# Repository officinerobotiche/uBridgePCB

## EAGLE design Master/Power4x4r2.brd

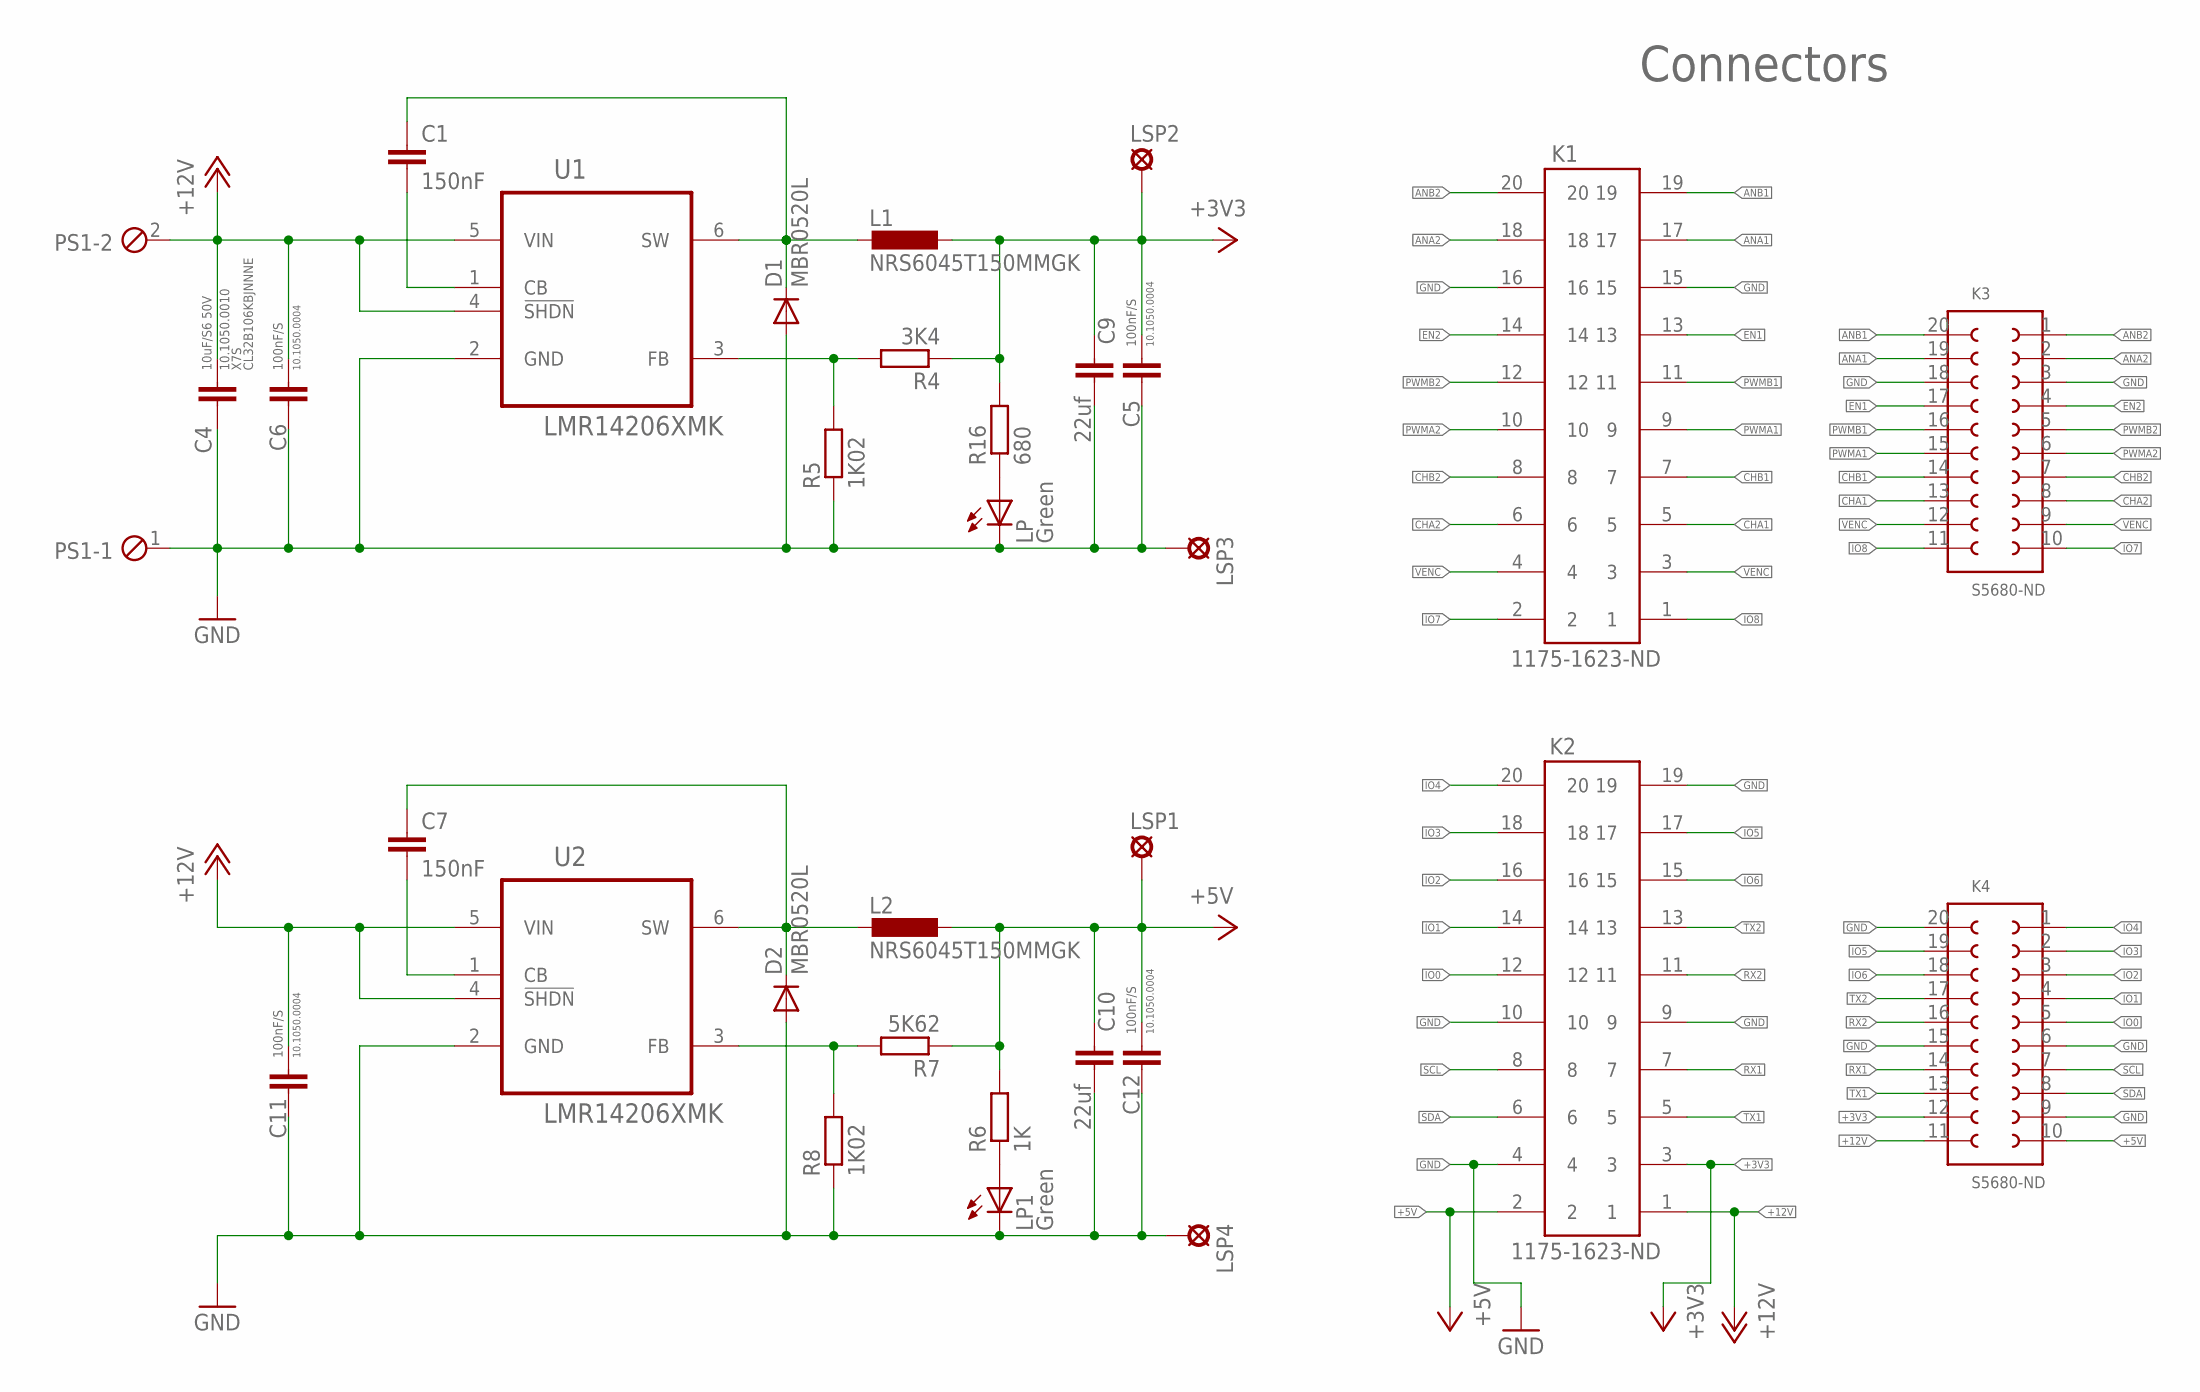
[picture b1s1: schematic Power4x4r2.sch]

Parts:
C1, C7: 150nF; C0805K
C4: 10uF/S6 50V; C3225
C5, C6, C11, C12: 100nF/S; C0805
C9, C10: 22uf; C1206
D1, D2: MBR0520L; SOD123; DIGIKEY MBR0520LCT-ND
K1, K2: 1175-1623-ND; 612X2020621
K3, K4: S5680-ND; 61002021821
L1, L2: NRS6045T150MMGK; POWER-CHOKE_WE-TPC; DIGIKEY 587-2948-1-ND
LP, LP1: Green; CHIPLED_0805
LSP1, LSP2, LSP3, LSP4: LSP10
PS1: MPT2; 2POL254
R4: 3K4; R0805
R5, R8: 1K02; R0805
R6: 1K; R0603
R7: 5K62; R0805
R16: 680; R0603
U1, U2: LMR14206XMK; SOT95P280X110-6N; DIGIKEY LMR14206XMKE/NOPBCT-ND

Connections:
+3V3: C5.2, C9.1, K2.3, K4.12, L1.1, LSP2.MP, R4.1, R16.2
+5V: C10.1, C12.2, K2.2, K4.10, L2.1, LSP1.MP, R6.2, R7.1
+12V: C4.1, C6.2, C11.2, K2.1, K4.11, PS1.2, U1.4 (!SHDN), U1.5 (VIN), U2.4 (!SHDN), U2.5 (VIN)
ANA1: K1.17, K3.19
ANA2: K1.18, K3.2
ANB1: K1.19, K3.20
ANB2: K1.20, K3.1
CHA1: K1.5, K3.13
CHA2: K1.6, K3.8
CHB1: K1.7, K3.14
CHB2: K1.8, K3.7
EN1: K1.13, K3.17
EN2: K1.14, K3.4
GND: C4.2, C5.1, C6.1, C9.2, C10.2, C11.1, C12.1, D1.A, D2.A, K1.15, K1.16, K2.4, K2.9, K2.10, K2.19, K3.3, K3.18, K4.6, K4.9, K4.15, K4.20, LP.C, LP1.C, LSP3.MP, LSP4.MP, PS1.1, R5.1, R8.1, U1.2 (GND), U2.2 (GND)
IO0: K2.12, K4.5
IO1: K2.14, K4.4
IO2: K2.16, K4.3
IO3: K2.18, K4.2
IO4: K2.20, K4.1
IO5: K2.17, K4.19
IO6: K2.15, K4.18
IO7: K1.2, K3.10
IO8: K1.1, K3.11
unnamed: C1.2, U1.1 (CB)
unnamed: C1.1, D1.C, L1.2, U1.6 (SW)
unnamed: LP1.A, R6.1
unnamed: R4.2, R5.2, U1.3 (FB)
unnamed: LP.A, R16.1
unnamed: C7.2, U2.1 (CB)
unnamed: C7.1, D2.C, L2.2, U2.6 (SW)
unnamed: R7.2, R8.2, U2.3 (FB)
PWMA1: K1.9, K3.15
PWMA2: K1.10, K3.6
PWMB1: K1.11, K3.16
PWMB2: K1.12, K3.5
RX1: K2.7, K4.14
RX2: K2.11, K4.16
SCL: K2.8, K4.7
SDA: K2.6, K4.8
TX1: K2.5, K4.13
TX2: K2.13, K4.17
VENC: K1.3, K1.4, K3.9, K3.12

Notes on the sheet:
Connectors

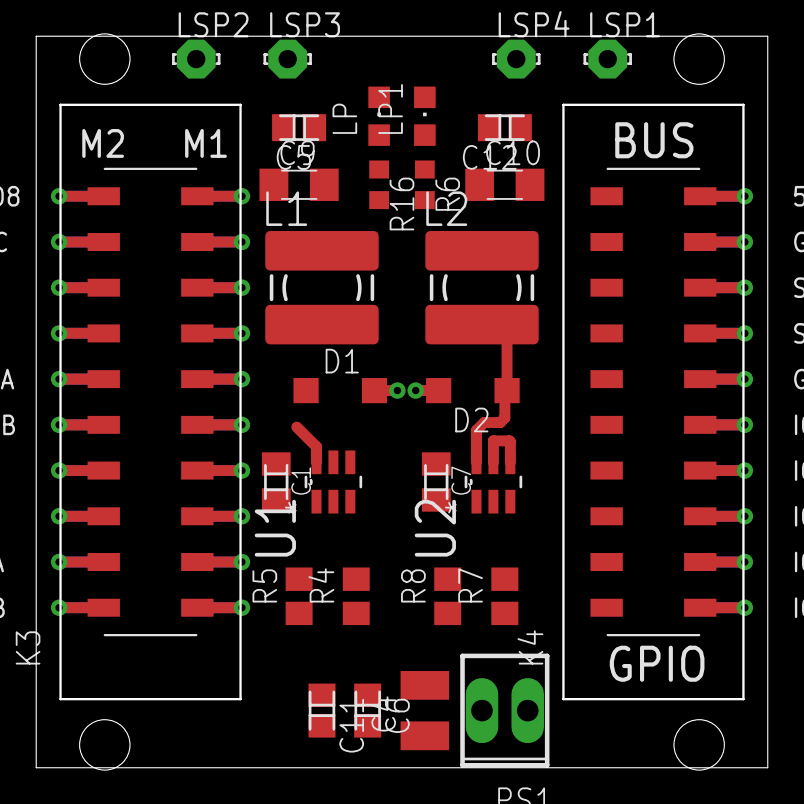
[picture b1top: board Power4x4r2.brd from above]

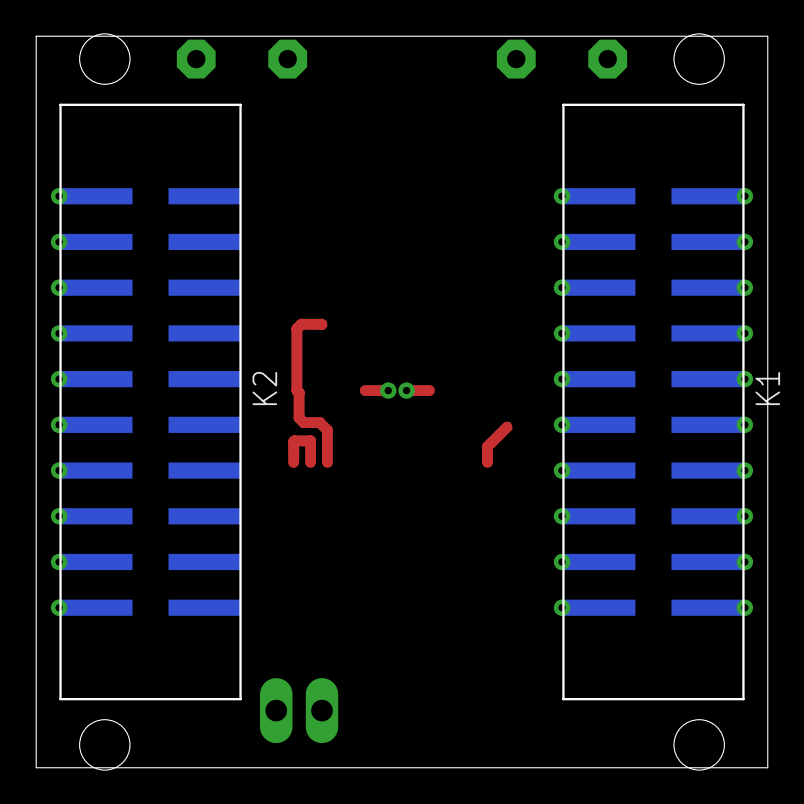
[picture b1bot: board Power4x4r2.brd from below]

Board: 2 copper layers, 40.6 x 40.6 mm, 32 parts (2 on the bottom side), 42 nets.

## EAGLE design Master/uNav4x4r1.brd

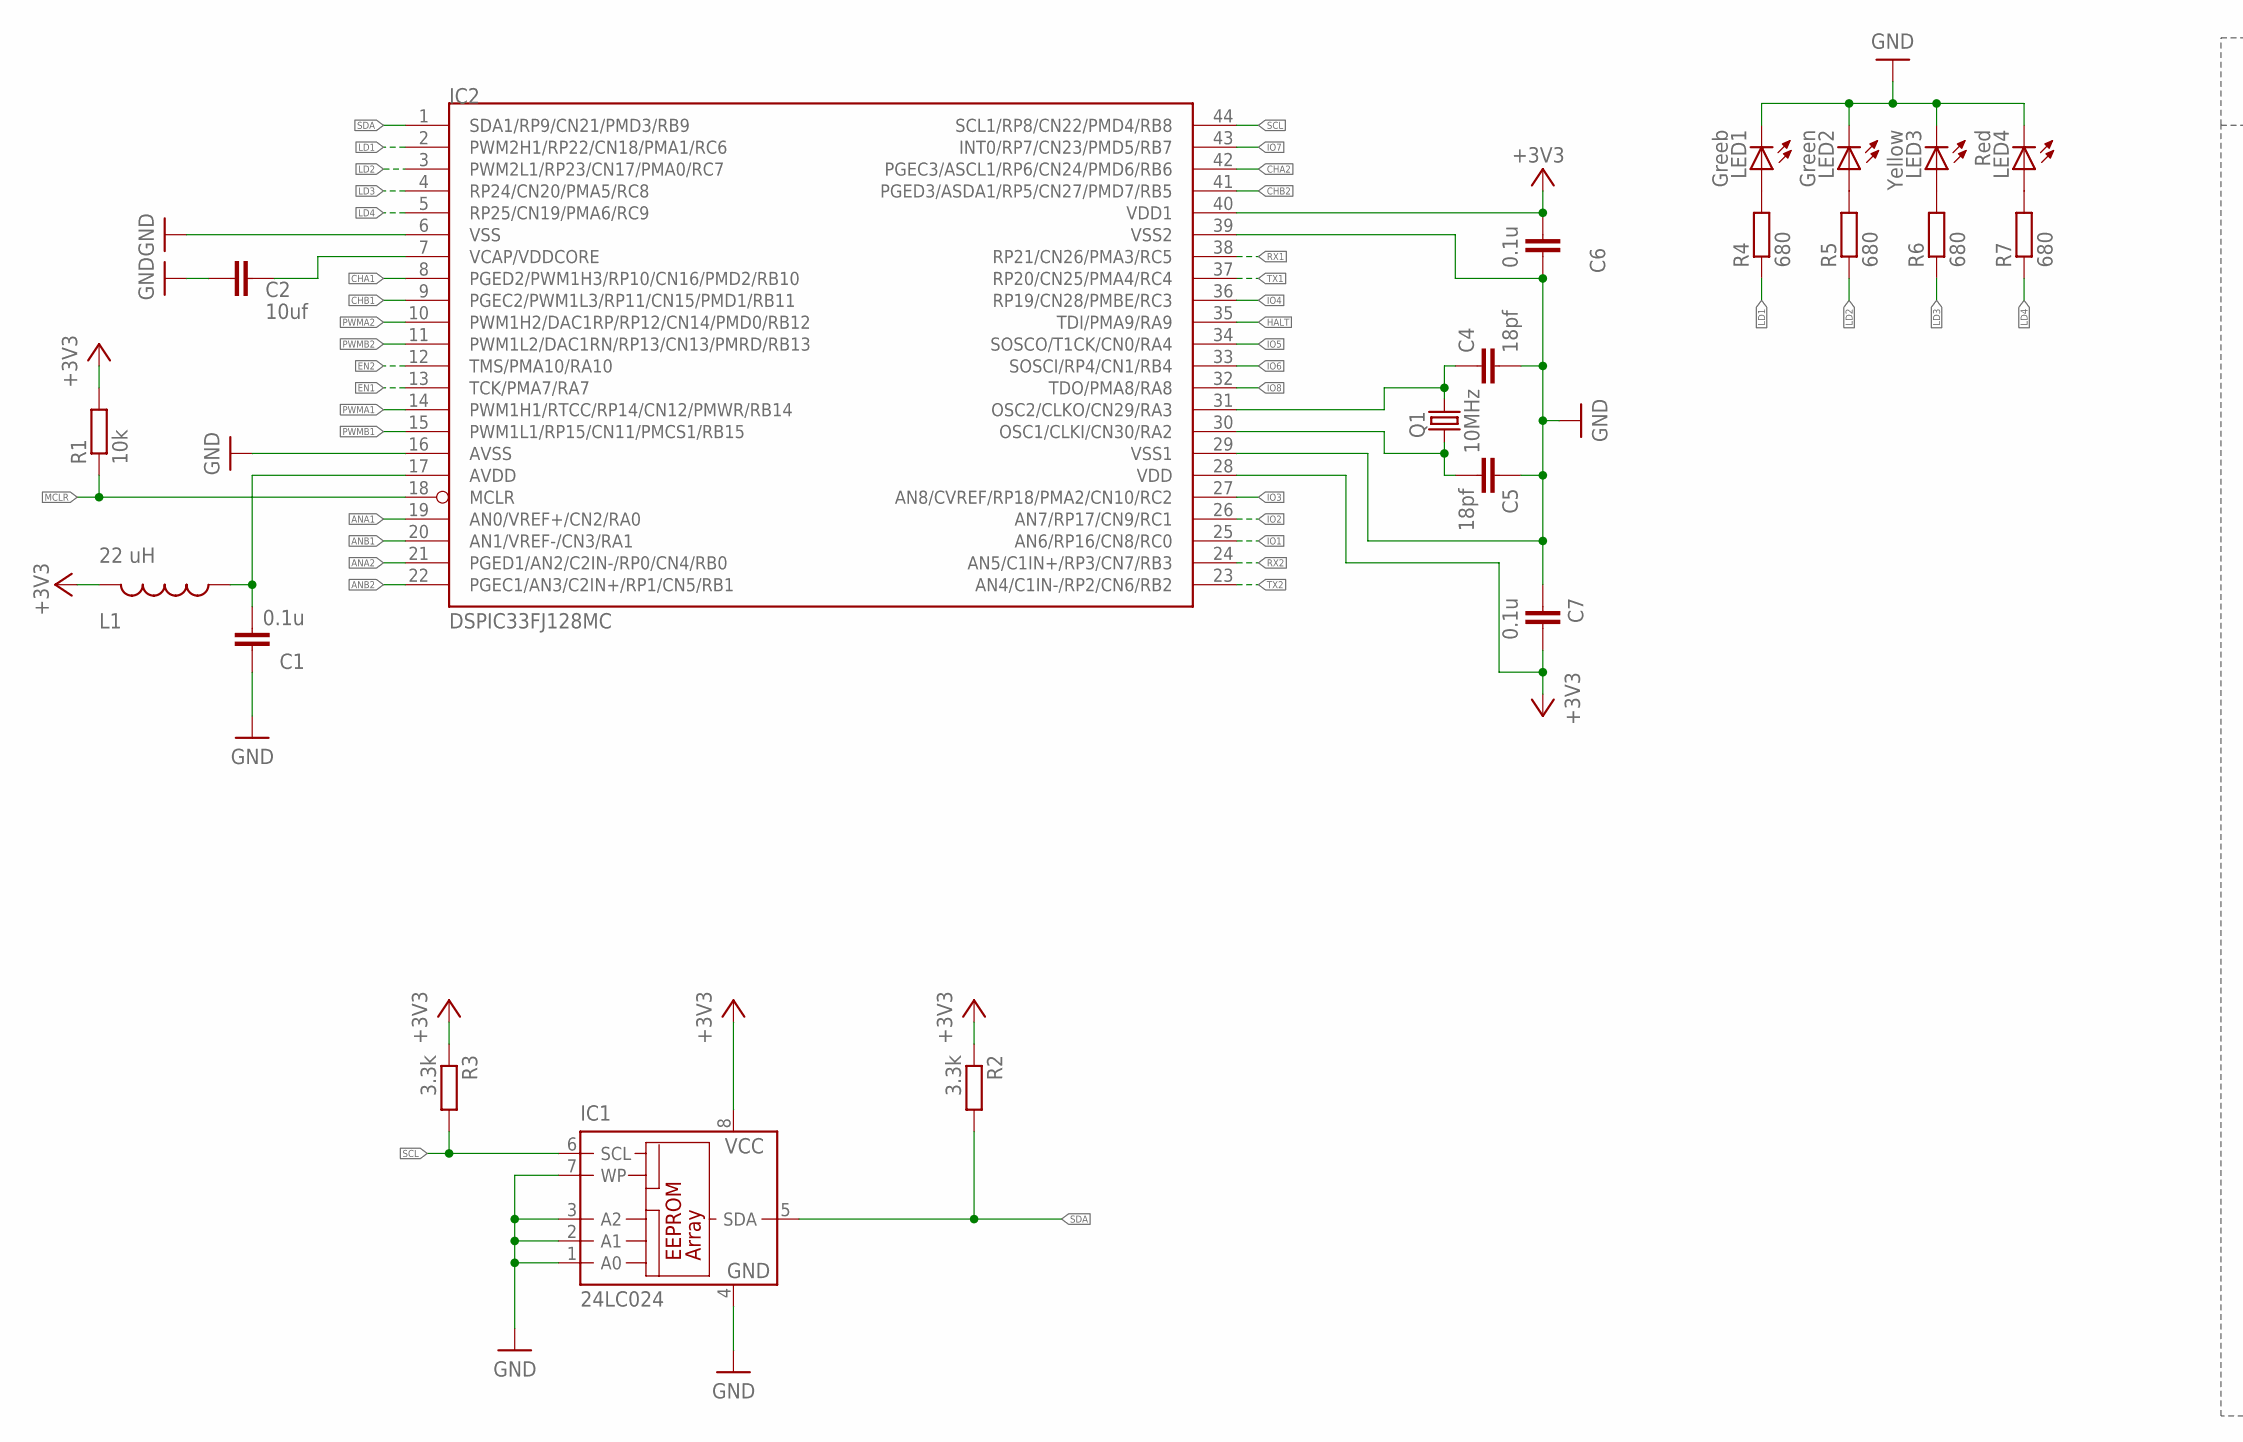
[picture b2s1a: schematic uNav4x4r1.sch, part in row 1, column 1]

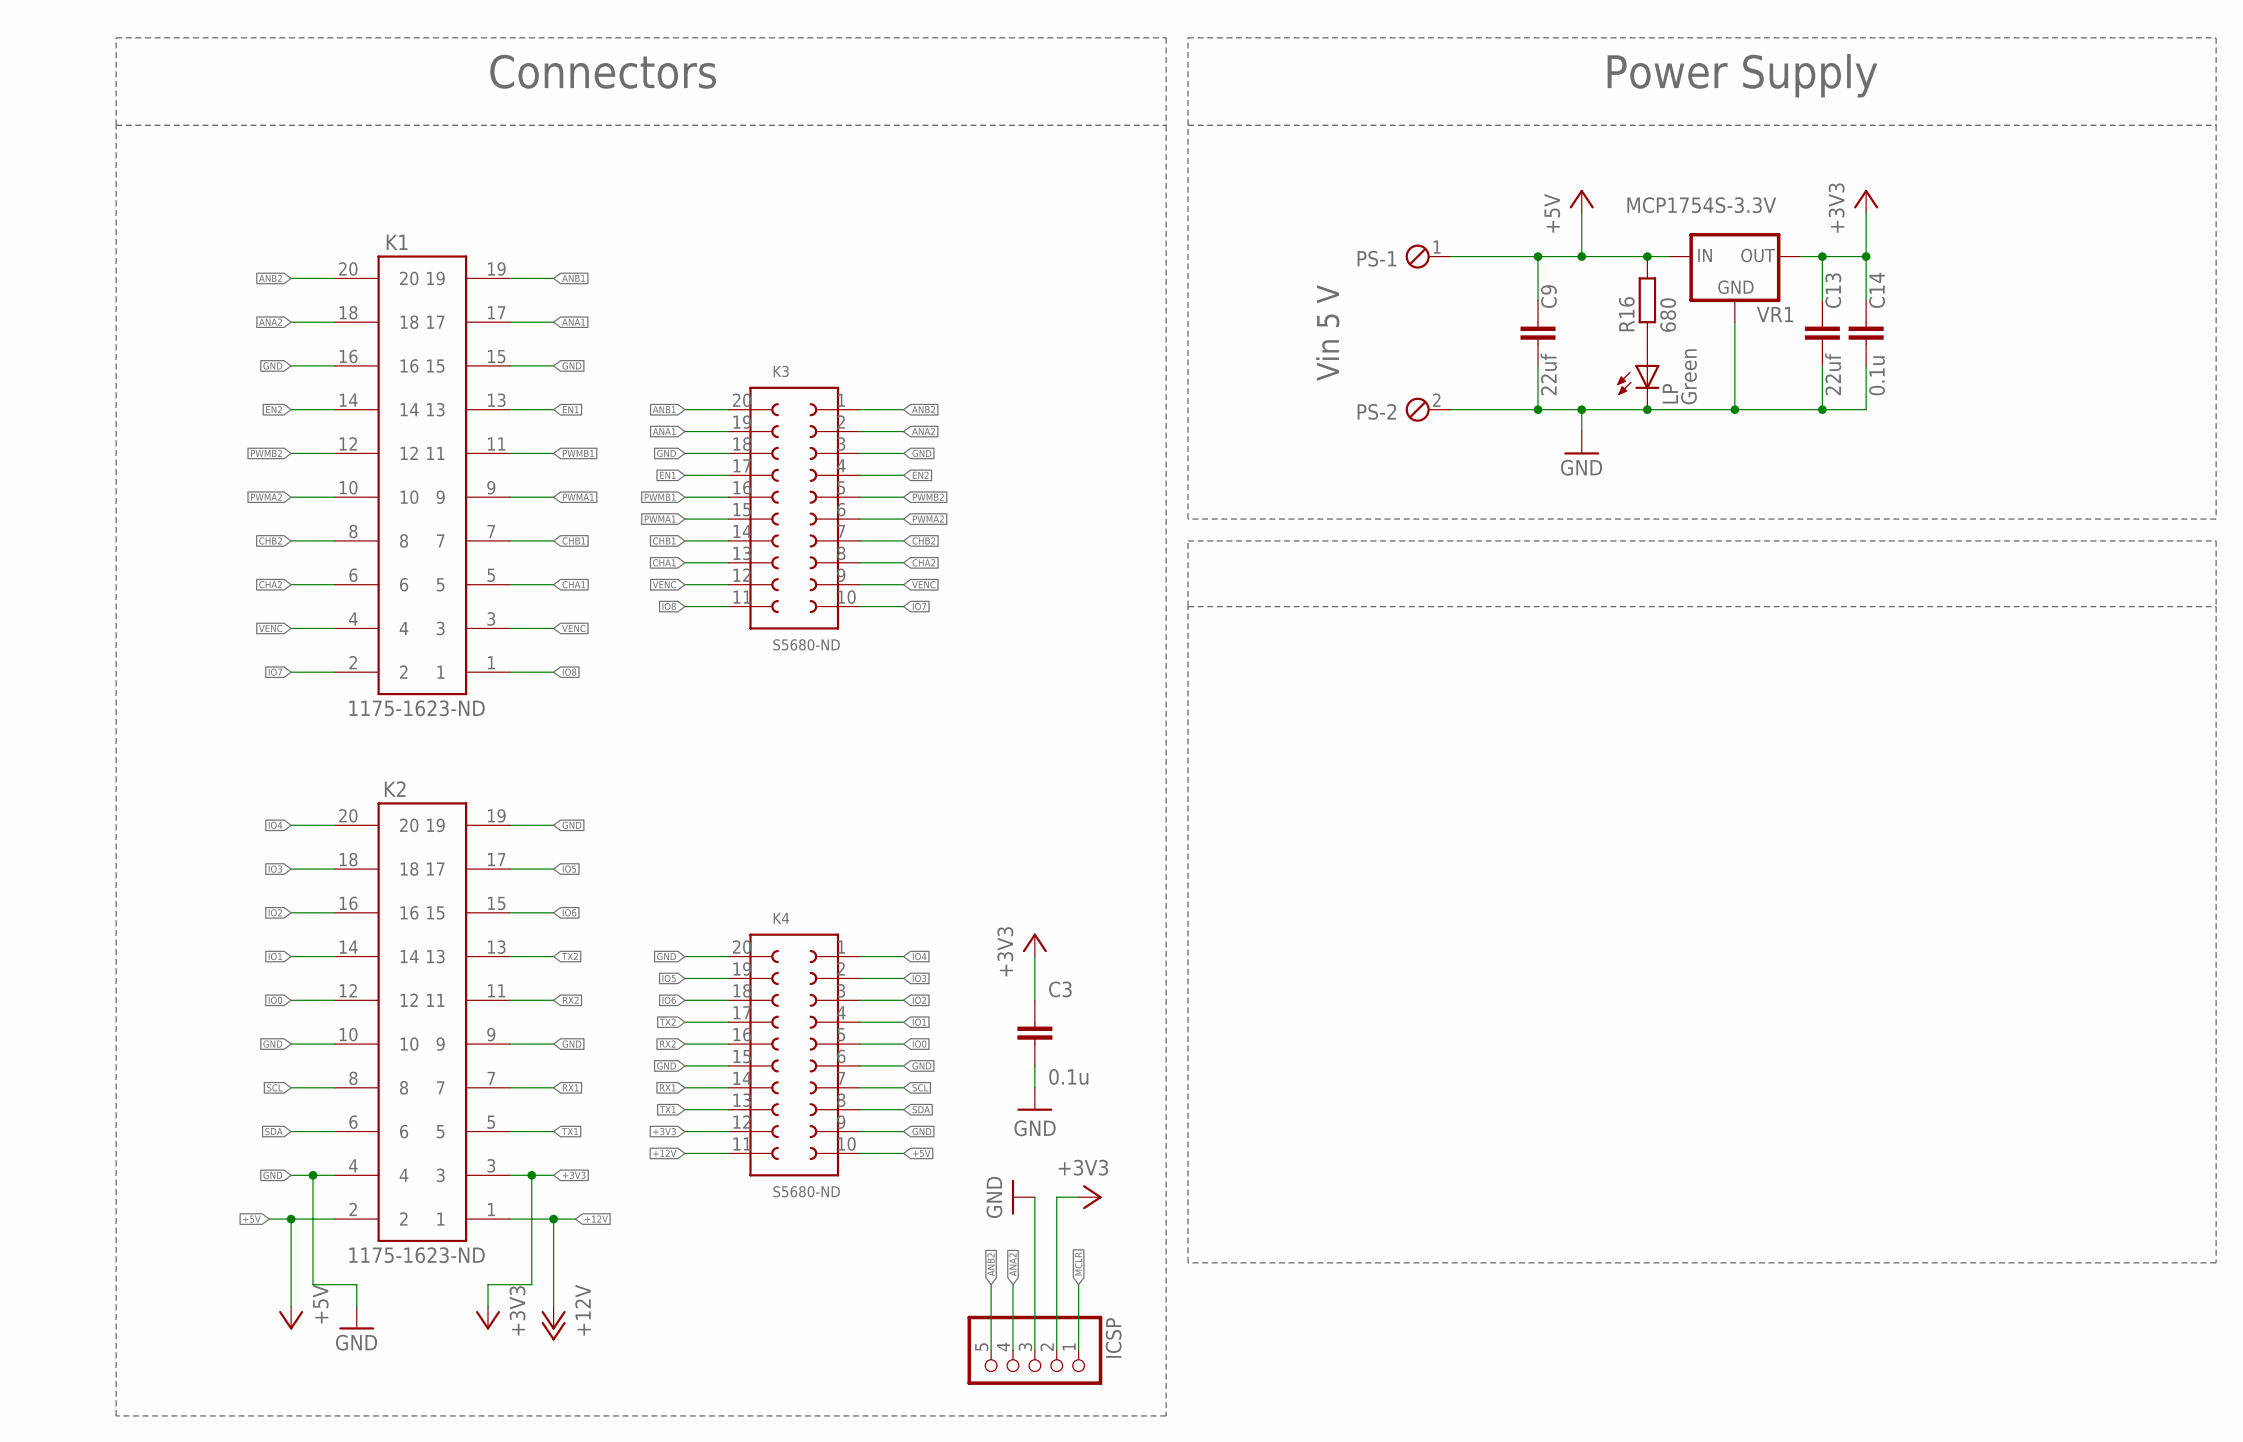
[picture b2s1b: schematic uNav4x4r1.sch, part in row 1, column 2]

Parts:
C1, C3, C6, C7, C14: 0.1u; C0603
C2: 10uf; C1206
C4, C5: 18pf; C0603
C9, C13: 22uf; C1206
IC1: 24LC024; SO-08M
IC2: DSPIC33FJ128MC; TQFP44
ICSP: PINHD-1X05_2.54-S; 1X05-S
K1, K2: 1175-1623-ND; 612X2020621
K3, K4: S5680-ND; 61002021821
L1: 22 uH; 0805
LED1: Greeb; CHIPLED_0805
LED2: Green; CHIPLED_0805
LED3: Yellow; CHIPLED_0805
LED4: Red; CHIPLED_0805
LP: Green; CHIPLED_0805
PS: MPT2; 2POL254
Q1: 10MHz; HC49U-V
R1: 10k; R0603
R2, R3: 3.3k; R0603
R4, R5, R6, R7, R16: 680; R0603
VR1: MCP1754S-3.3V; SOT89

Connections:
+3V3: C3.1, C6.2, C7.1, C13.1, C14.1, IC1.8 (VCC), IC2.28 (VDD), IC2.40 (VDD1), ICSP.2, K2.3, K4.12, L1.2, R1.2, R2.1, R3.1, VR1.3 (OUT)
+5V: C9.1, K2.2, K4.10, PS.1, R16.2, VR1.1 (IN)
+12V: K2.1, K4.11
ANA1: IC2.19 (AN0/VREF+/CN2/RA0), K1.17, K3.19
ANA2: IC2.21 (PGED1/AN2/C2IN-/RP0/CN4/RB0), ICSP.4, K1.18, K3.2
ANB1: IC2.20 (AN1/VREF-/CN3/RA1), K1.19, K3.20
ANB2: IC2.22 (PGEC1/AN3/C2IN+/RP1/CN5/RB1), ICSP.5, K1.20, K3.1
AVDD: C1.2, IC2.17 (AVDD), L1.1
CHA1: IC2.8 (PGED2/PWM1H3/RP10/CN16/PMD2/RB10), K1.5, K3.13
CHA2: IC2.42 (PGEC3/ASCL1/RP6/CN24/PMD6/RB6), K1.6, K3.8
CHB1: IC2.9 (PGEC2/PWM1L3/RP11/CN15/PMD1/RB11), K1.7, K3.14
CHB2: IC2.41 (PGED3/ASDA1/RP5/CN27/PMD7/RB5), K1.8, K3.7
EN1: IC2.13 (TCK/PMA7/RA7), K1.13, K3.17
EN2: IC2.12 (TMS/PMA10/RA10), K1.14, K3.4
GND: C1.1, C2.2, C3.2, C4.2, C5.1, C6.1, C7.2, C9.2, C13.2, C14.2, IC1.1 (A0), IC1.2 (A1), IC1.3 (A2), IC1.4 (GND), IC1.7 (WP), IC2.6 (VSS), IC2.16 (AVSS), IC2.29 (VSS1), IC2.39 (VSS2), ICSP.3, K1.15, K1.16, K2.4, K2.9, K2.10, K2.19, K3.3, K3.18, K4.6, K4.9, K4.15, K4.20, LED1.C, LED2.C, LED3.C, LED4.C, LP.C, PS.2, VR1.2 (GND), VR1.4 (GND)
HALT: IC2.35 (TDI/PMA9/RA9)
IO0: K2.12, K4.5
IO1: IC2.25 (AN6/RP16/CN8/RC0), K2.14, K4.4
IO2: IC2.26 (AN7/RP17/CN9/RC1), K2.16, K4.3
IO3: IC2.27 (AN8/CVREF/RP18/PMA2/CN10/RC2), K2.18, K4.2
IO4: IC2.36 (RP19/CN28/PMBE/RC3), K2.20, K4.1
IO5: IC2.34 (SOSCO/T1CK/CN0/RA4), K2.17, K4.19
IO6: IC2.33 (SOSCI/RP4/CN1/RB4), K2.15, K4.18
IO7: IC2.43 (INT0/RP7/CN23/PMD5/RB7), K1.2, K3.10
IO8: IC2.32 (TDO/PMA8/RA8), K1.1, K3.11
LD1: IC2.2 (PWM2H1/RP22/CN18/PMA1/RC6), R4.1
LD2: IC2.3 (PWM2L1/RP23/CN17/PMA0/RC7), R5.1
LD3: IC2.4 (RP24/CN20/PMA5/RC8), R6.1
LD4: IC2.5 (RP25/CN19/PMA6/RC9), R7.1
MCLR: IC2.18 (MCLR), ICSP.1, R1.1
unnamed: C5.2, IC2.30 (OSC1/CLKI/CN30/RA2), Q1.1
unnamed: C4.1, IC2.31 (OSC2/CLKO/CN29/RA3), Q1.2
unnamed: LP.A, R16.1
unnamed: LED1.A, R4.2
unnamed: LED2.A, R5.2
unnamed: LED3.A, R6.2
unnamed: LED4.A, R7.2
PWMA1: IC2.14 (PWM1H1/RTCC/RP14/CN12/PMWR/RB14), K1.9, K3.15
PWMA2: IC2.10 (PWM1H2/DAC1RP/RP12/CN14/PMD0/RB12), K1.10, K3.6
PWMB1: IC2.15 (PWM1L1/RP15/CN11/PMCS1/RB15), K1.11, K3.16
PWMB2: IC2.11 (PWM1L2/DAC1RN/RP13/CN13/PMRD/RB13), K1.12, K3.5
RX1: IC2.38 (RP21/CN26/PMA3/RC5), K2.7, K4.14
RX2: IC2.24 (AN5/C1IN+/RP3/CN7/RB3), K2.11, K4.16
SCL: IC1.6 (SCL), IC2.44 (SCL1/RP8/CN22/PMD4/RB8), K2.8, K4.7, R3.2
SDA: IC1.5 (SDA), IC2.1 (SDA1/RP9/CN21/PMD3/RB9), K2.6, K4.8, R2.2
TX1: IC2.37 (RP20/CN25/PMA4/RC4), K2.5, K4.13
TX2: IC2.23 (AN4/C1IN-/RP2/CN6/RB2), K2.13, K4.17
VCAP/VDDCORE: C2.1, IC2.7 (VCAP/VDDCORE)
VENC: K1.3, K1.4, K3.9, K3.12

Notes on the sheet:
Connectors
Vin 5 V
Power Supply

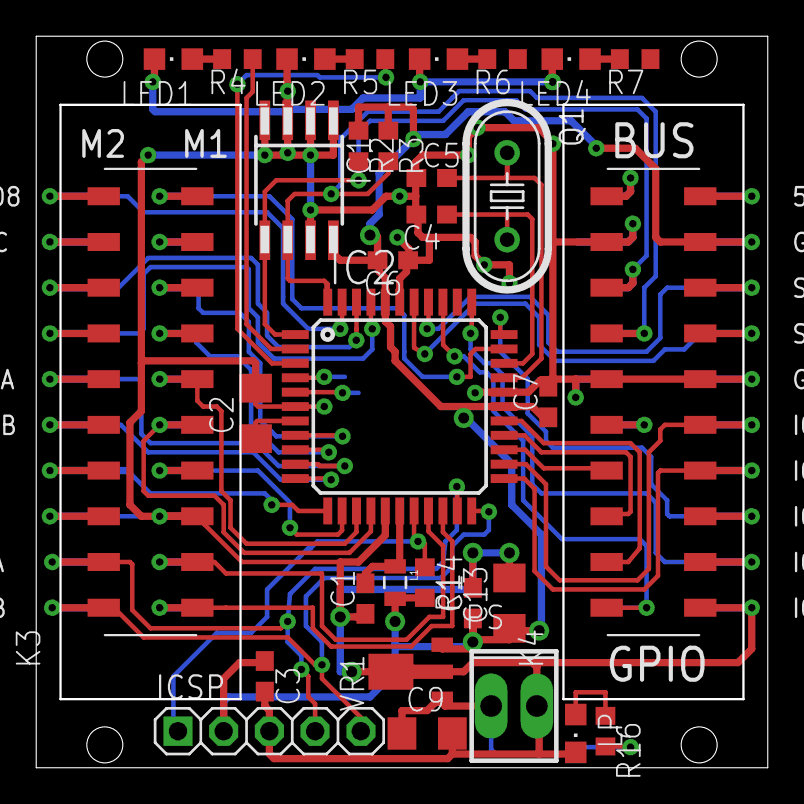
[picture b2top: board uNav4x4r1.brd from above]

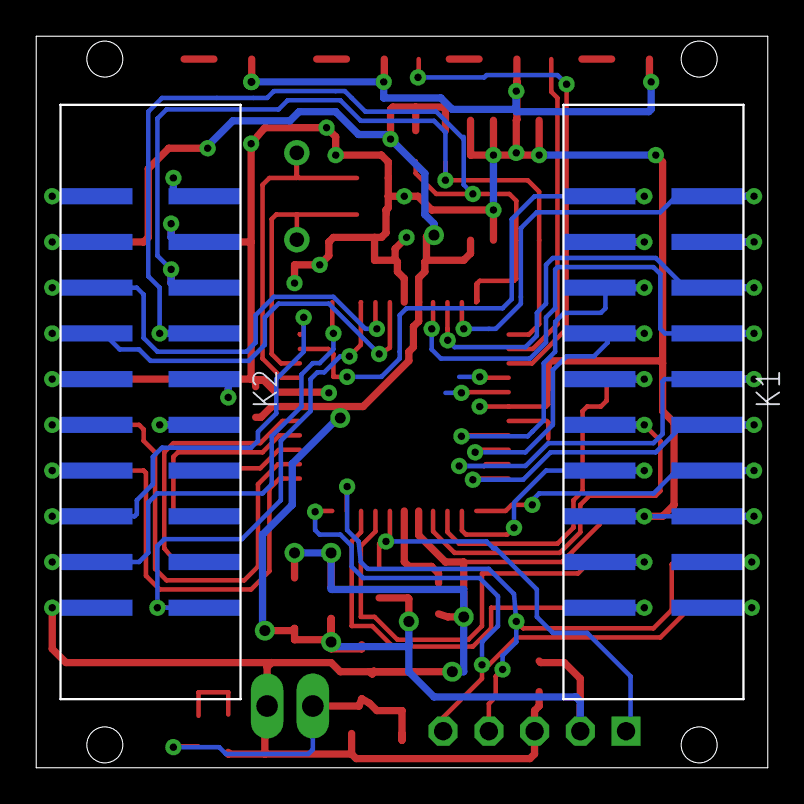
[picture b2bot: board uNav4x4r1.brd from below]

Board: 2 copper layers, 40.6 x 40.6 mm, 34 parts (2 on the bottom side), 48 nets.

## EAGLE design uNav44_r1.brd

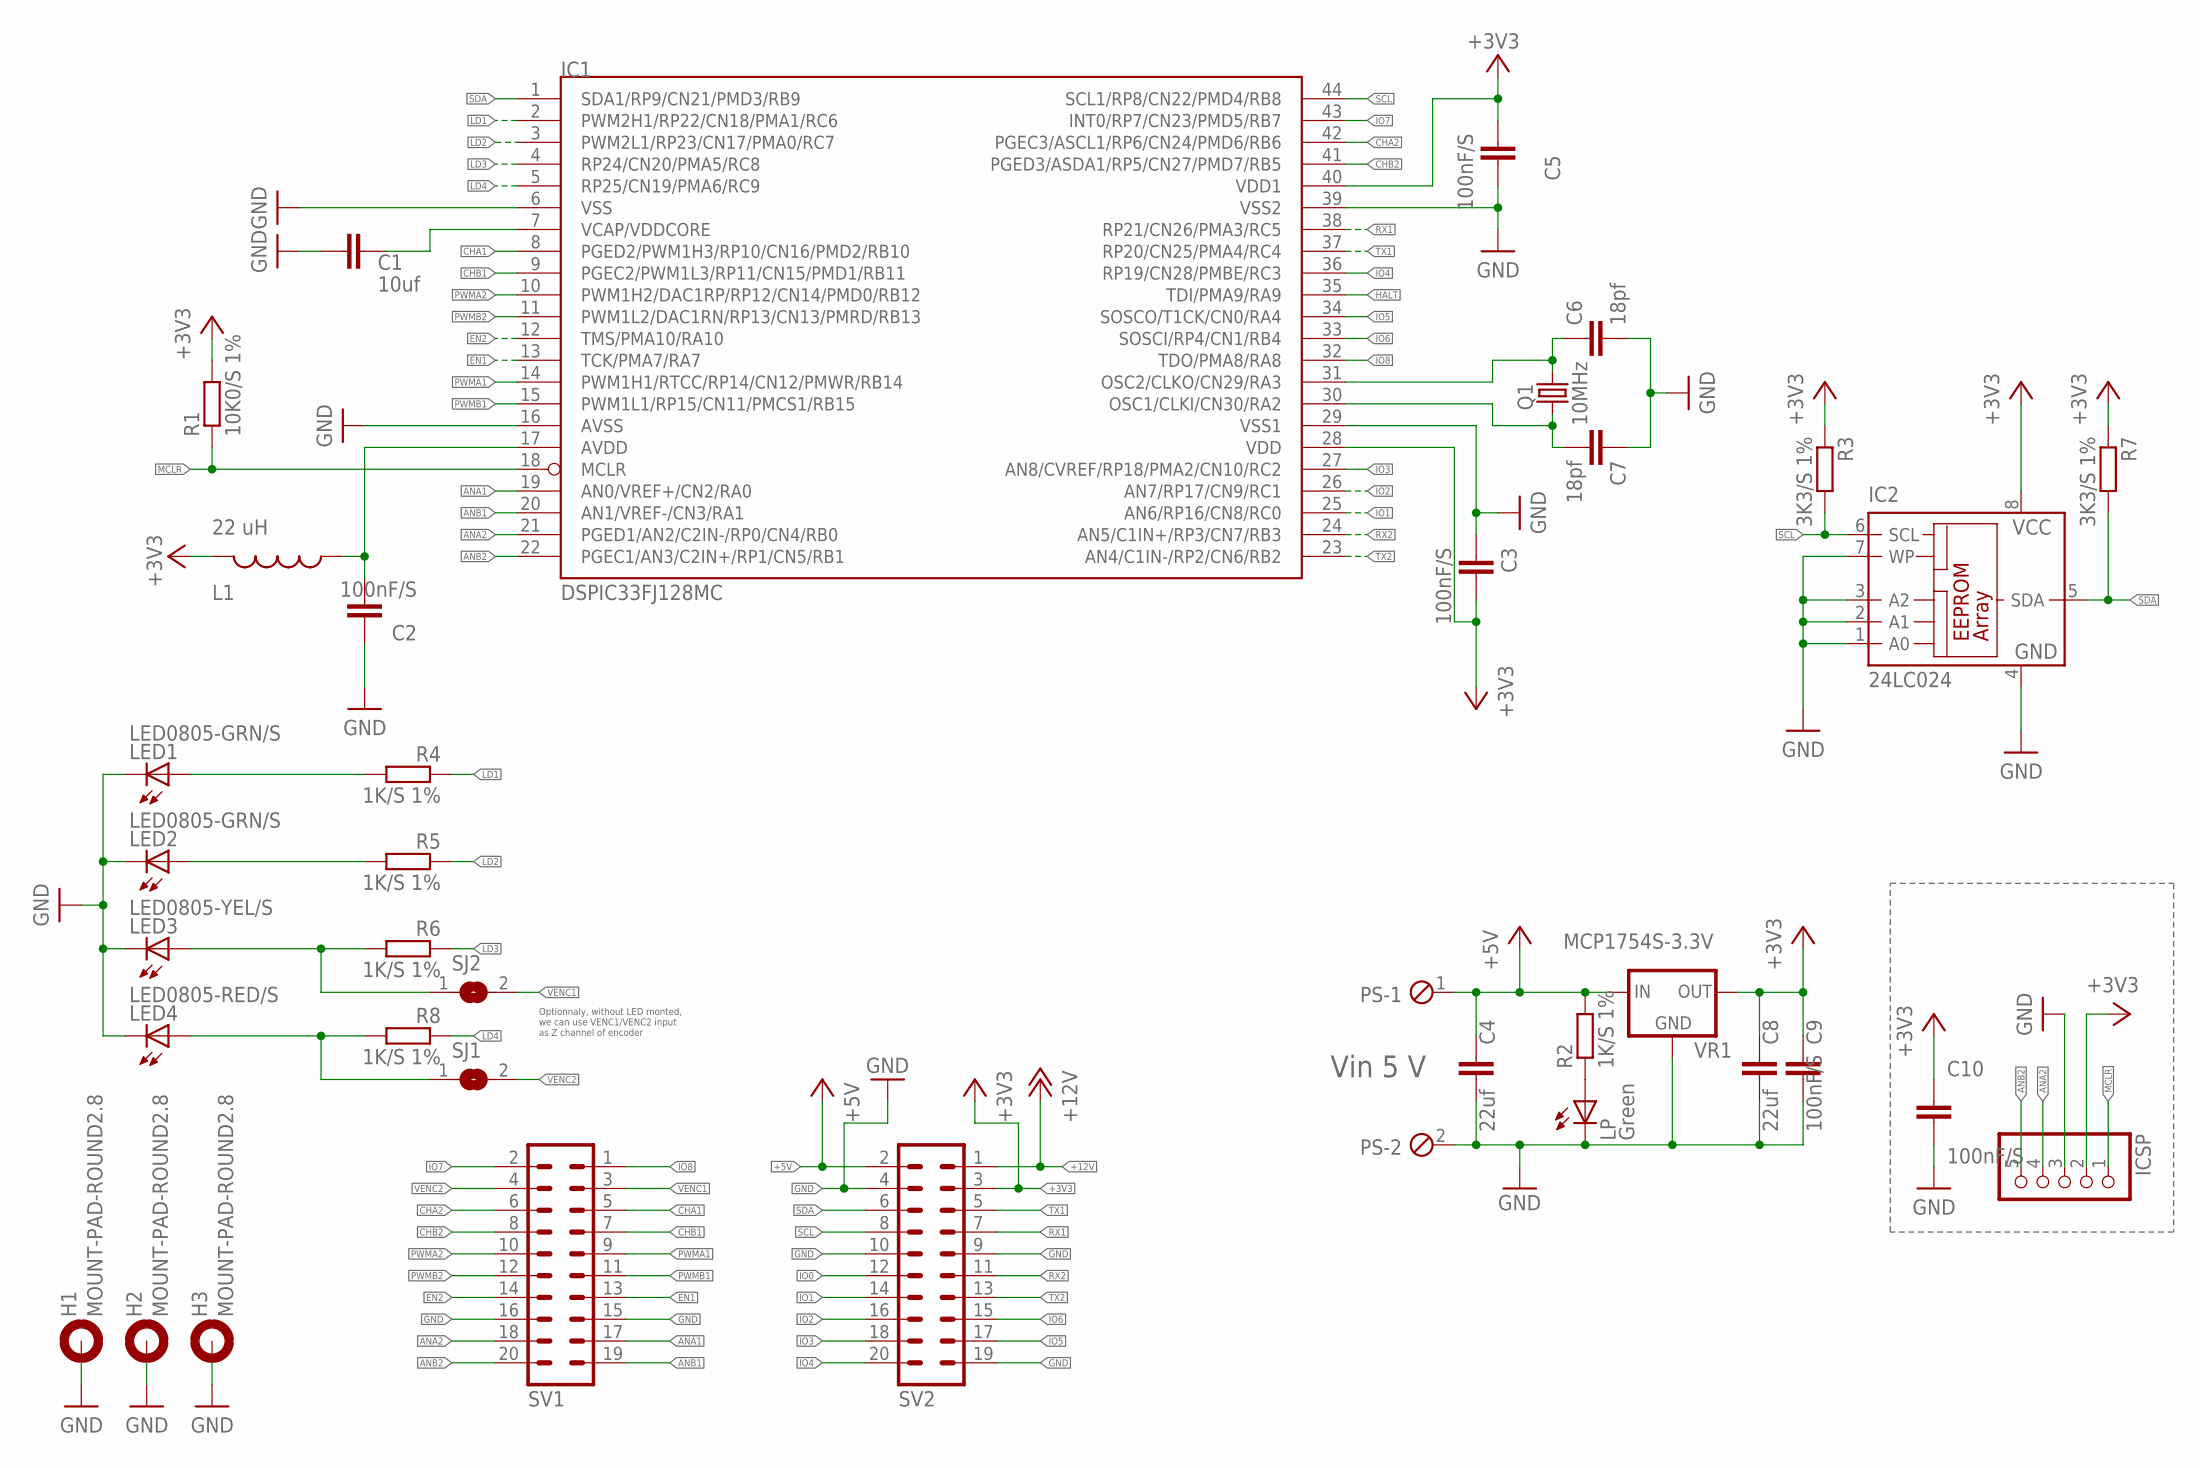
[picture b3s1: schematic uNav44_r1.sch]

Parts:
C1: 10uf; C1206
C2, C3, C5, C9, C10: 100nF/S; C0603
C4, C8: 22uf; C1206
C6, C7: 18pf; C0603
H1, H2, H3: MOUNT-PAD-ROUND2.8; 2,8-PAD
IC1: DSPIC33FJ128MC; TQFP44
IC2: 24LC024; SO-08M
ICSP: PINHD-1X05_2.54-S; 1X05-S
L1: 22 uH; 0805
LED1, LED2: LED0805-GRN/S; CHIPLED_0805
LED3: LED0805-YEL/S; CHIPLED_0805
LED4: LED0805-RED/S; CHIPLED_0805
LP: Green; CHIPLED_0805
PS: MPT2; 2POL254
Q1: 10MHz; HC49U-V
R1: 10K0/S 1%; R0603
R2, R4, R5, R6, R8: 1K/S 1%; R0603
R3, R7: 3K3/S 1%; R0603
SJ1, SJ2: SJ
SV1, SV2: MA10-2
VR1: MCP1754S-3.3V; SOT89

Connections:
+3V3: C3.1, C5.2, C8.1, C9.1, C10.1, IC1.28 (VDD), IC1.40 (VDD1), IC2.8 (VCC), ICSP.2, L1.2, R1.2, R3.1, R7.1, SV2.3, VR1.3 (OUT)
+5V: C4.1, PS.1, R2.2, SV2.2, VR1.1 (IN)
+12V: SV2.1
ANA1: IC1.19 (AN0/VREF+/CN2/RA0), SV1.17
ANA2: IC1.21 (PGED1/AN2/C2IN-/RP0/CN4/RB0), ICSP.4, SV1.18
ANB1: IC1.20 (AN1/VREF-/CN3/RA1), SV1.19
ANB2: IC1.22 (PGEC1/AN3/C2IN+/RP1/CN5/RB1), ICSP.5, SV1.20
AVDD: C2.2, IC1.17 (AVDD), L1.1
CHA1: IC1.8 (PGED2/PWM1H3/RP10/CN16/PMD2/RB10), SV1.5
CHA2: IC1.42 (PGEC3/ASCL1/RP6/CN24/PMD6/RB6), SV1.6
CHB1: IC1.9 (PGEC2/PWM1L3/RP11/CN15/PMD1/RB11), SV1.7
CHB2: IC1.41 (PGED3/ASDA1/RP5/CN27/PMD7/RB5), SV1.8
EN1: IC1.13 (TCK/PMA7/RA7), SV1.13
EN2: IC1.12 (TMS/PMA10/RA10), SV1.14
GND: C1.2, C2.1, C3.2, C4.2, C5.1, C6.2, C7.1, C8.2, C9.2, C10.2, H1.B2,8, H2.B2,8, H3.B2,8, IC1.6 (VSS), IC1.16 (AVSS), IC1.29 (VSS1), IC1.39 (VSS2), IC2.1 (A0), IC2.2 (A1), IC2.3 (A2), IC2.4 (GND), IC2.7 (WP), ICSP.3, LED1.C, LED2.C, LED3.C, LED4.C, LP.C, PS.2, SV1.15, SV1.16, SV2.4, SV2.9, SV2.10, SV2.19, VR1.2 (GND), VR1.4 (GND)
HALT: IC1.35 (TDI/PMA9/RA9)
IO0: SV2.12
IO1: IC1.25 (AN6/RP16/CN8/RC0), SV2.14
IO2: IC1.26 (AN7/RP17/CN9/RC1), SV2.16
IO3: IC1.27 (AN8/CVREF/RP18/PMA2/CN10/RC2), SV2.18
IO4: IC1.36 (RP19/CN28/PMBE/RC3), SV2.20
IO5: IC1.34 (SOSCO/T1CK/CN0/RA4), SV2.17
IO6: IC1.33 (SOSCI/RP4/CN1/RB4), SV2.15
IO7: IC1.43 (INT0/RP7/CN23/PMD5/RB7), SV1.2
IO8: IC1.32 (TDO/PMA8/RA8), SV1.1
LD1: IC1.2 (PWM2H1/RP22/CN18/PMA1/RC6), R4.1
LD2: IC1.3 (PWM2L1/RP23/CN17/PMA0/RC7), R5.1
LD3: IC1.4 (RP24/CN20/PMA5/RC8), R6.1
LD4: IC1.5 (RP25/CN19/PMA6/RC9), R8.1
MCLR: IC1.18 (MCLR), ICSP.1, R1.1
unnamed: C7.2, IC1.30 (OSC1/CLKI/CN30/RA2), Q1.1
unnamed: C6.1, IC1.31 (OSC2/CLKO/CN29/RA3), Q1.2
unnamed: LP.A, R2.1
unnamed: LED1.A, R4.2
unnamed: LED2.A, R5.2
PWMA1: IC1.14 (PWM1H1/RTCC/RP14/CN12/PMWR/RB14), SV1.9
PWMA2: IC1.10 (PWM1H2/DAC1RP/RP12/CN14/PMD0/RB12), SV1.10
PWMB1: IC1.15 (PWM1L1/RP15/CN11/PMCS1/RB15), SV1.11
PWMB2: IC1.11 (PWM1L2/DAC1RN/RP13/CN13/PMRD/RB13), SV1.12
RX1: IC1.38 (RP21/CN26/PMA3/RC5), SV2.7
RX2: IC1.24 (AN5/C1IN+/RP3/CN7/RB3), SV2.11
SCL: IC1.44 (SCL1/RP8/CN22/PMD4/RB8), IC2.6 (SCL), R3.2, SV2.8
SDA: IC1.1 (SDA1/RP9/CN21/PMD3/RB9), IC2.5 (SDA), R7.2, SV2.6
TX1: IC1.37 (RP20/CN25/PMA4/RC4), SV2.5
TX2: IC1.23 (AN4/C1IN-/RP2/CN6/RB2), SV2.13
VCAP/VDDCORE: C1.1, IC1.7 (VCAP/VDDCORE)
VENC1: SJ2.2, SV1.3
VENC1-LD3: LED3.A, R6.2, SJ2.1
VENC2: SJ1.2, SV1.4
VENC2-LD4: LED4.A, R8.2, SJ1.1

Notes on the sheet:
Vin 5 V
Optionnaly, without LED monted, we can use VENC1/VENC2 input as Z channel of encoder

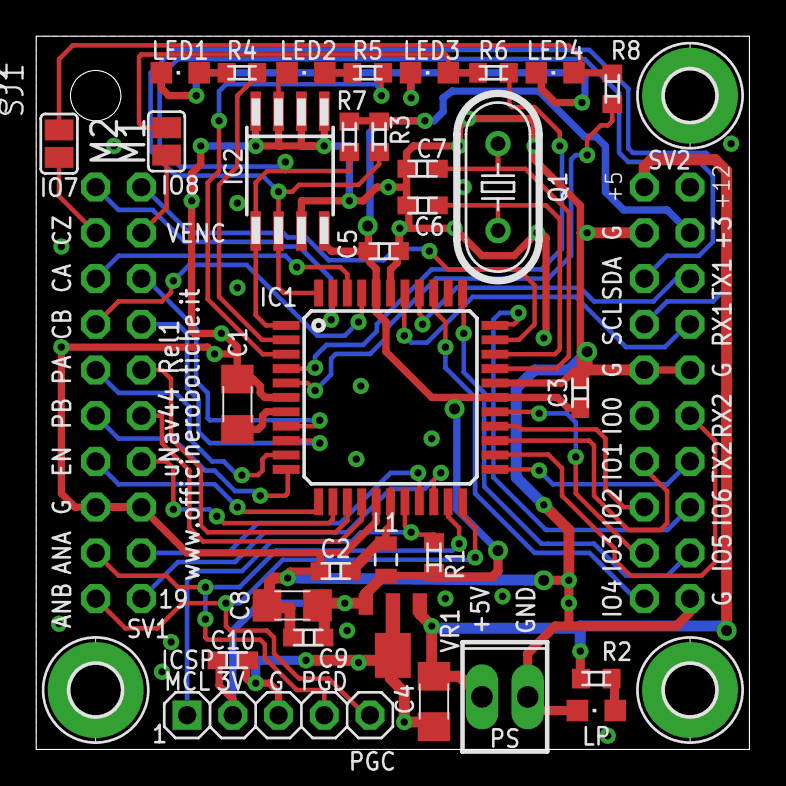
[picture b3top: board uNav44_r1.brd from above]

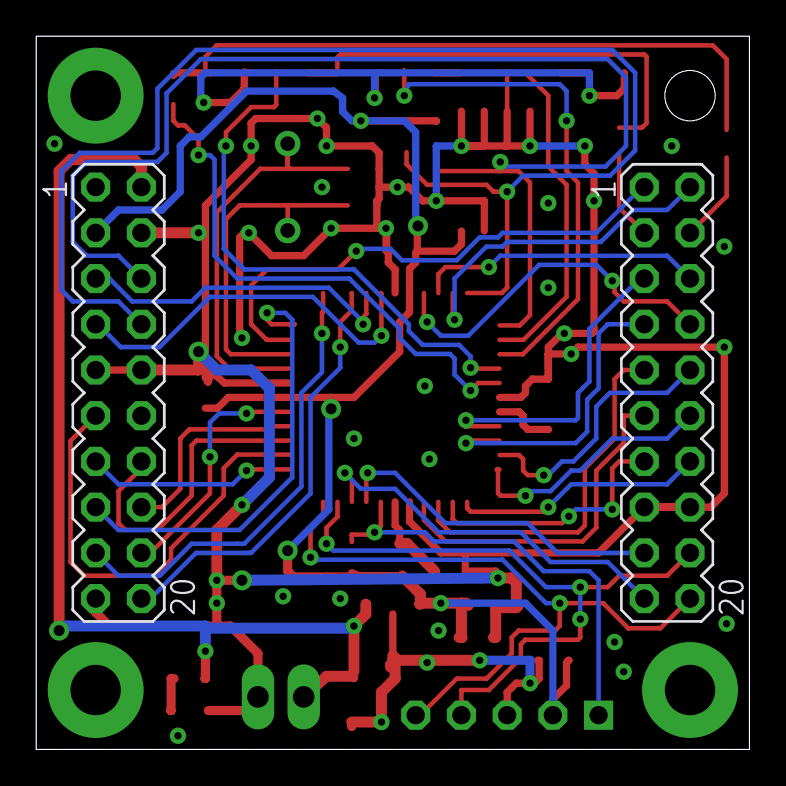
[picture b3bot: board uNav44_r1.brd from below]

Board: 2 copper layers, 39.6 x 39.6 mm, 37 parts (2 on the bottom side), 47 nets.

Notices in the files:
parts and their libraries:
Wuerth_Elektronik_eiCan_Wire_to_Board_Co: Copyright: Würth Elektronik
SparkFun-Passives: Licensing: Creative Commons ShareAlike 4.0 International - https://creativecommons.org/licenses/by-sa/4.0
